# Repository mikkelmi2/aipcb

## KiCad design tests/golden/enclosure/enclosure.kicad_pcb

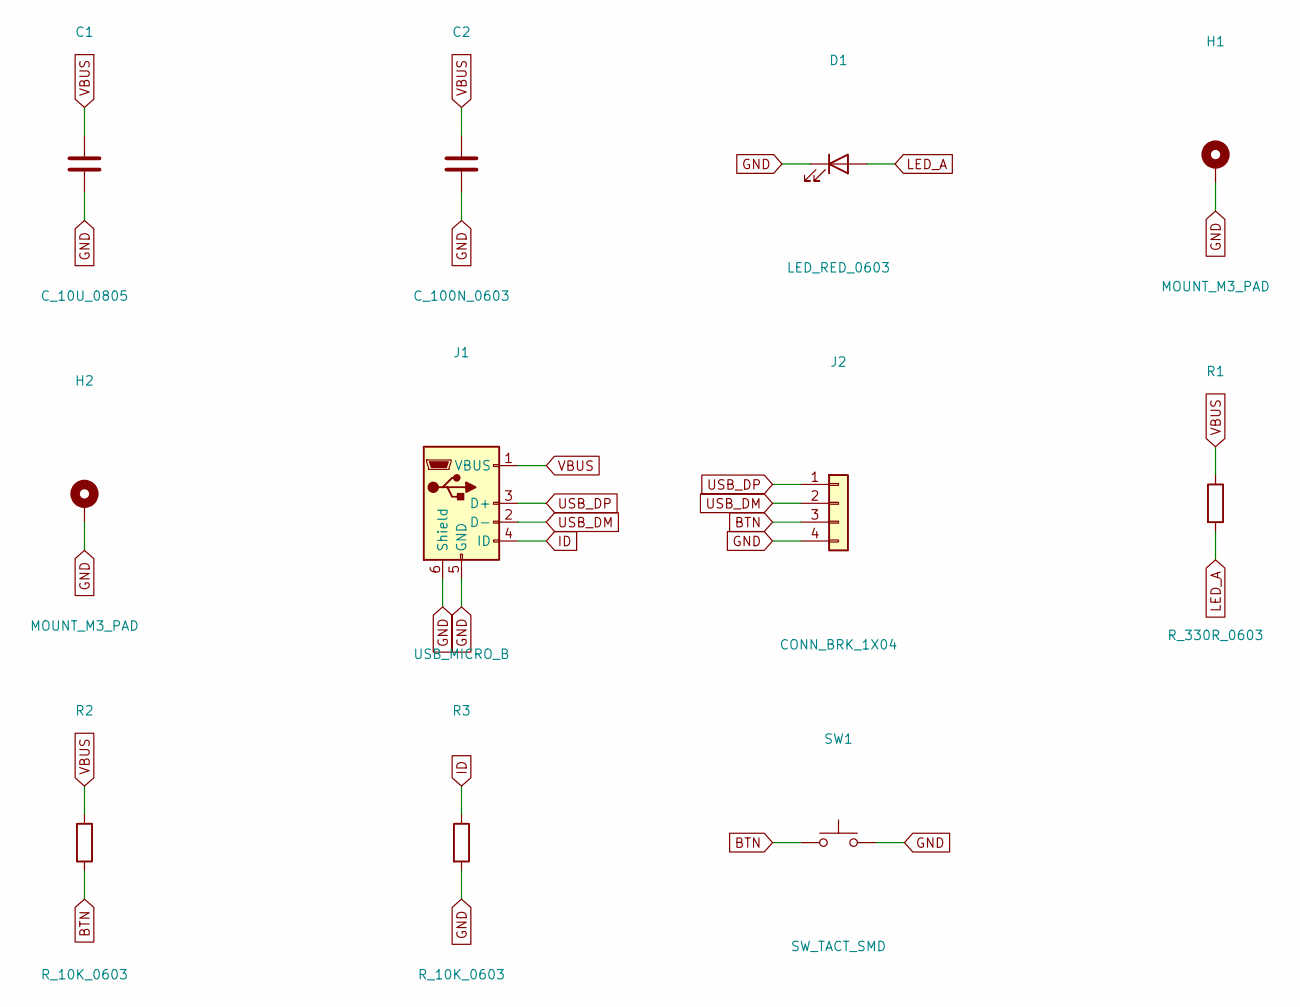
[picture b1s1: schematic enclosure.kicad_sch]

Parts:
C1: C_10U_0805; C_0805_2012Metric
C2: C_100N_0603; C_0603_1608Metric
D1: LED_RED_0603; LED_0603_1608Metric
H1, H2: MOUNT_M3_PAD; MountingHole_3.2mm_M3_Pad
J1: USB_MICRO_B; USB_Micro-B_Amphenol_10103594-0001LF_Horizontal
J2: CONN_BRK_1X04; PinHeader_1x04_P2.54mm_Vertical
R1: R_330R_0603; R_0603_1608Metric
R2, R3: R_10K_0603; R_0603_1608Metric
SW1: SW_TACT_SMD; SW_SPST_B3S-1000

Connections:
BTN: J2.3, R2.2, SW1.1
GND: C1.2, C2.2, D1.1 (K), H1.1, H2.1, J1.5 (GND), J1.6 (Shield), J2.4, R3.2, SW1.2
ID: J1.4 (ID), R3.1
LED_A: D1.2 (A), R1.2
USB_DM: J1.2 (D-), J2.2
USB_DP: J1.3 (D+), J2.1
VBUS: C1.1, C2.1, J1.1 (VBUS), R1.1, R2.1

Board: 2 copper layers, 11 parts (0 on the bottom side), 7 nets, no tracks yet.

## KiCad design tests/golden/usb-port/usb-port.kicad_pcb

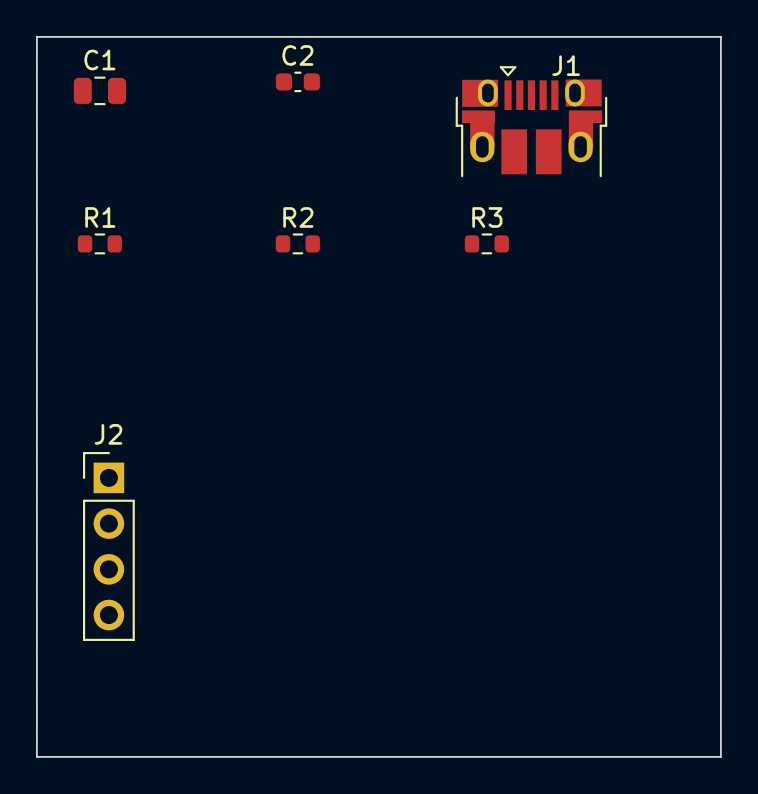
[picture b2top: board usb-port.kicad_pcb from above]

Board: 2 copper layers, 38.0 x 40.0 mm, 7 parts (0 on the bottom side), 7 nets, no tracks yet.

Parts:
C1: C_10U_0805; C_0805_2012Metric
C2: C_100N_0603; C_0603_1608Metric
J1: USB_MICRO_B; USB_Micro-B_Amphenol_10103594-0001LF_Horizontal
J2: CONN_BRK_1X04; PinHeader_1x04_P2.54mm_Vertical
R1, R2: R_22R_0603; R_0603_1608Metric
R3: R_10K_0603; R_0603_1608Metric

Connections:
DEV_DM: J2.3, R2.2
DEV_DP: J2.2, R1.2
GND: C1.2, C2.2, J1.5, J1.6, J2.4, R3.2
ID: J1.4, R3.1
USB_DM: J1.2, R2.1
USB_DP: J1.3, R1.1
VBUS: C1.1, C2.1, J1.1, J2.1
